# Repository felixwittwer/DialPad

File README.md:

<br>
<br>

<div align="center">

</div>

<br>

# DialPad
a small Macropad with 9 keys, a rotary encoder and a small oled screen.

Now a screenshot with a lot of elemnts inside Fosion to make it look cool.

<br>
<br>
<br>

I have designed the to part to be this green color but I am probably printign it transparent with my SLA Esin printer so the left area doesn't look so empty. If translucent you can see some electronics 👀.

## PCB and Schematics

Some nice and clean schematics and a my PCB design. Nothing to creative but it has a little touch of Hacclub in it.

## Assembly

Just a very cool animation on how to assemble the DialPad. 

## Firmware

KMK with support for the dial and OLED screen. I will maybe further develop the firmware with macros and layers which will be shown on the screen but for now ith will be a numpad with a media controll dial.

- KMK

## BOM

- 9x Cherry MX Switches
- 9x DSA Keycaps
- 4x M3x16mm screws (heated inserts are not needed I am printing with SLA and Resin so threads are already in the design)
- 9x 1N4148 DO-35 Diodes.
- 1x 0.91" 128x32 OLED Display
- 1x EC11 Rotary Encoder
- 1x XIAO RP2040
- 1x Case (3 printed parts)

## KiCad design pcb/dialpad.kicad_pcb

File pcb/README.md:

# PCB

this folder contains all stuff regarding the PCB.

## Schematics

## PCB design

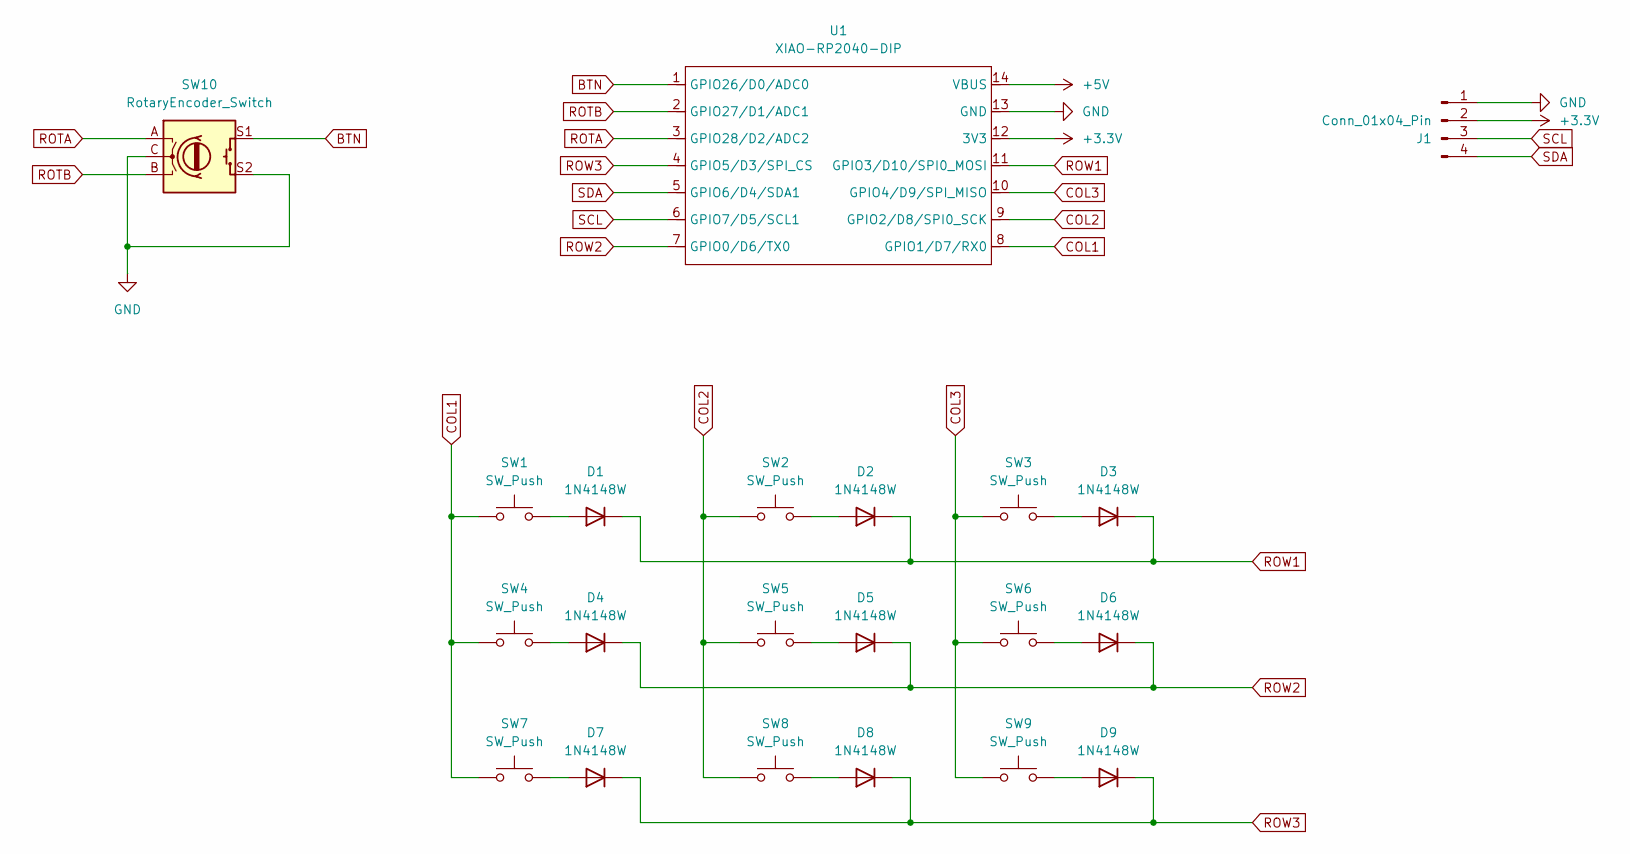
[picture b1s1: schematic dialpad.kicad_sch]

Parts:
D1, D2, D3, D4, D5, D6, D7, D8, D9: 1N4148W; D_A-405_P2.54mm_Vertical_AnodeUp
J1: Conn_01x04_Pin; PinSocket_1x04_P2.54mm_Vertical
SW1, SW2, SW3, SW4, SW5, SW6, SW7, SW8, SW9: SW_Push; SW_Cherry_MX_1.00u_PCB
SW10: RotaryEncoder_Switch; RotaryEncoder_Alps_EC11E-Switch_Vertical_H20mm_CircularMoun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
U1: XIAO-RP2040-DIP

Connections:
+3.3V: J1.2, U1.12 (3V3)
+5V: U1.14 (VBUS)
BTN: SW10.S1, U1.1 (GPIO26/D0/ADC0)
COL1: SW1.1, SW4.1, SW7.1, U1.8 (GPIO1/D7/RX0)
COL2: SW2.1, SW5.1, SW8.1, U1.9 (GPIO2/D8/SPI0_SCK)
COL3: SW3.1, SW6.1, SW9.1, U1.10 (GPIO4/D9/SPI_MISO)
GND: J1.1, SW10.C, SW10.S2, U1.13 (GND)
unnamed: D1.2 (A), SW1.2
unnamed: D2.2 (A), SW2.2
unnamed: D3.2 (A), SW3.2
unnamed: D4.2 (A), SW4.2
unnamed: D5.2 (A), SW5.2
unnamed: D6.2 (A), SW6.2
unnamed: D7.2 (A), SW7.2
unnamed: D8.2 (A), SW8.2
unnamed: D9.2 (A), SW9.2
ROTA: SW10.A, U1.3 (GPIO28/D2/ADC2)
ROTB: SW10.B, U1.2 (GPIO27/D1/ADC1)
ROW1: D1.1 (K), D2.1 (K), D3.1 (K), U1.11 (GPIO3/D10/SPI0_MOSI)
ROW2: D4.1 (K), D5.1 (K), D6.1 (K), U1.7 (GPIO0/D6/TX0)
ROW3: D7.1 (K), D8.1 (K), D9.1 (K), U1.4 (GPIO5/D3/SPI_CS)
SCL: J1.3, U1.6 (GPIO7/D5/SCL1)
SDA: J1.4, U1.5 (GPIO6/D4/SDA1)

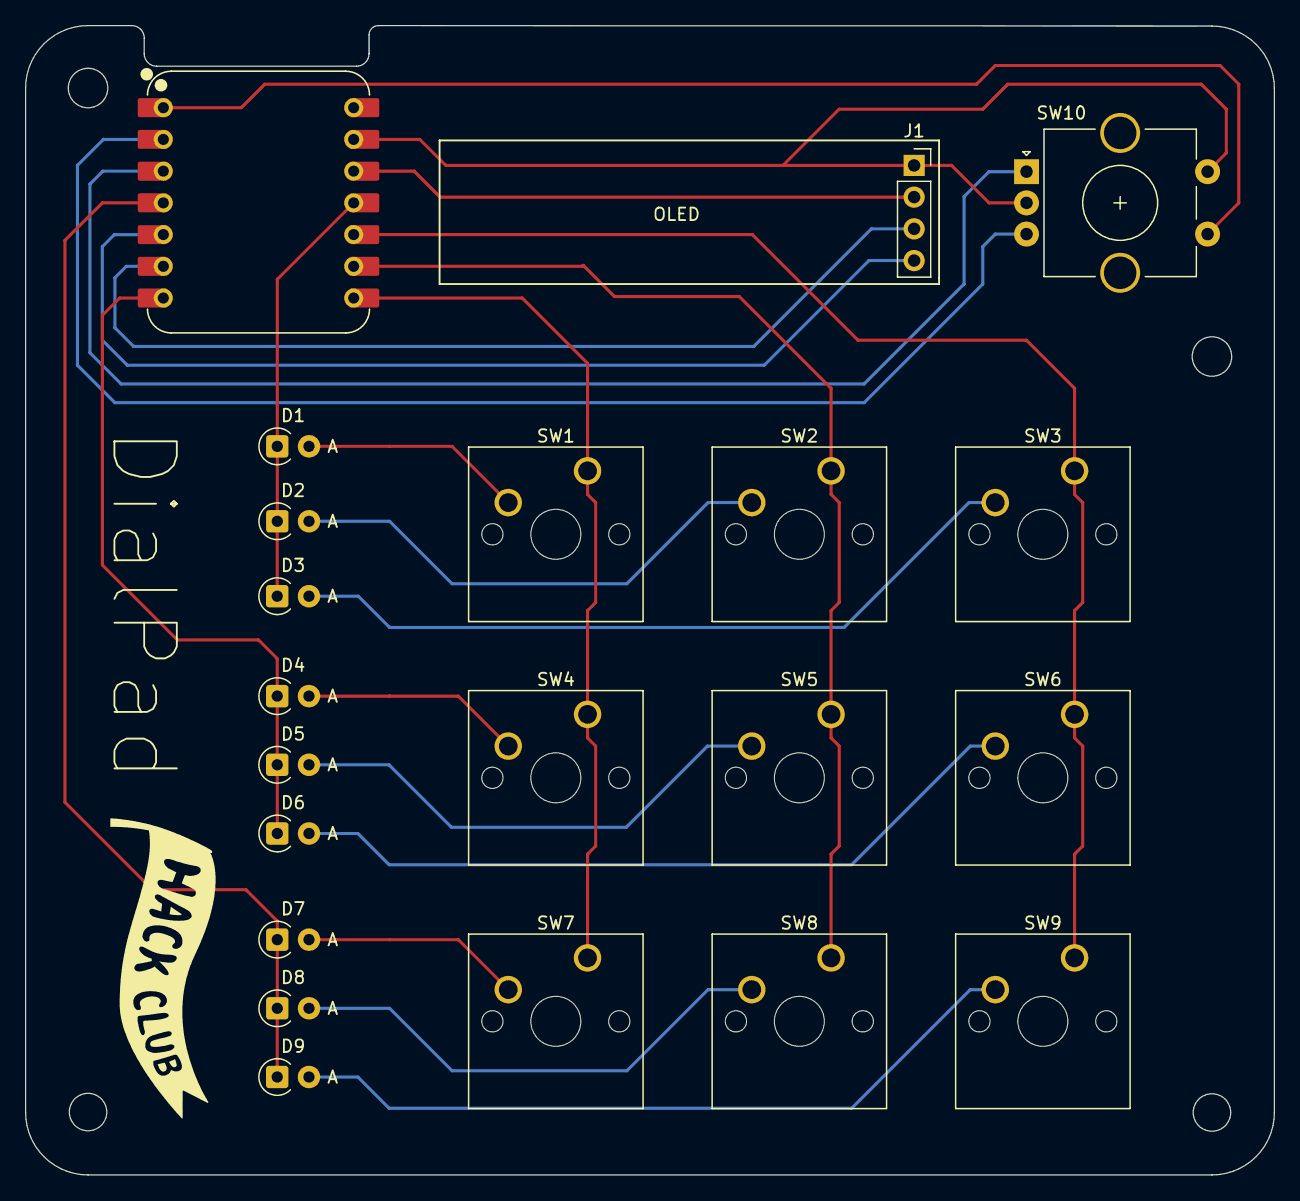
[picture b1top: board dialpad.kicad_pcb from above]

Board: 2 copper layers, 100.0 x 92.0 mm, 21 parts (0 on the bottom side), 22 nets.

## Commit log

2025-07-02 adding lots of stuff (almost everything) - PCB - CAD - Documentation
2025-07-02 fixing README bages
2025-07-03 add firmware and touch ups on PCB
